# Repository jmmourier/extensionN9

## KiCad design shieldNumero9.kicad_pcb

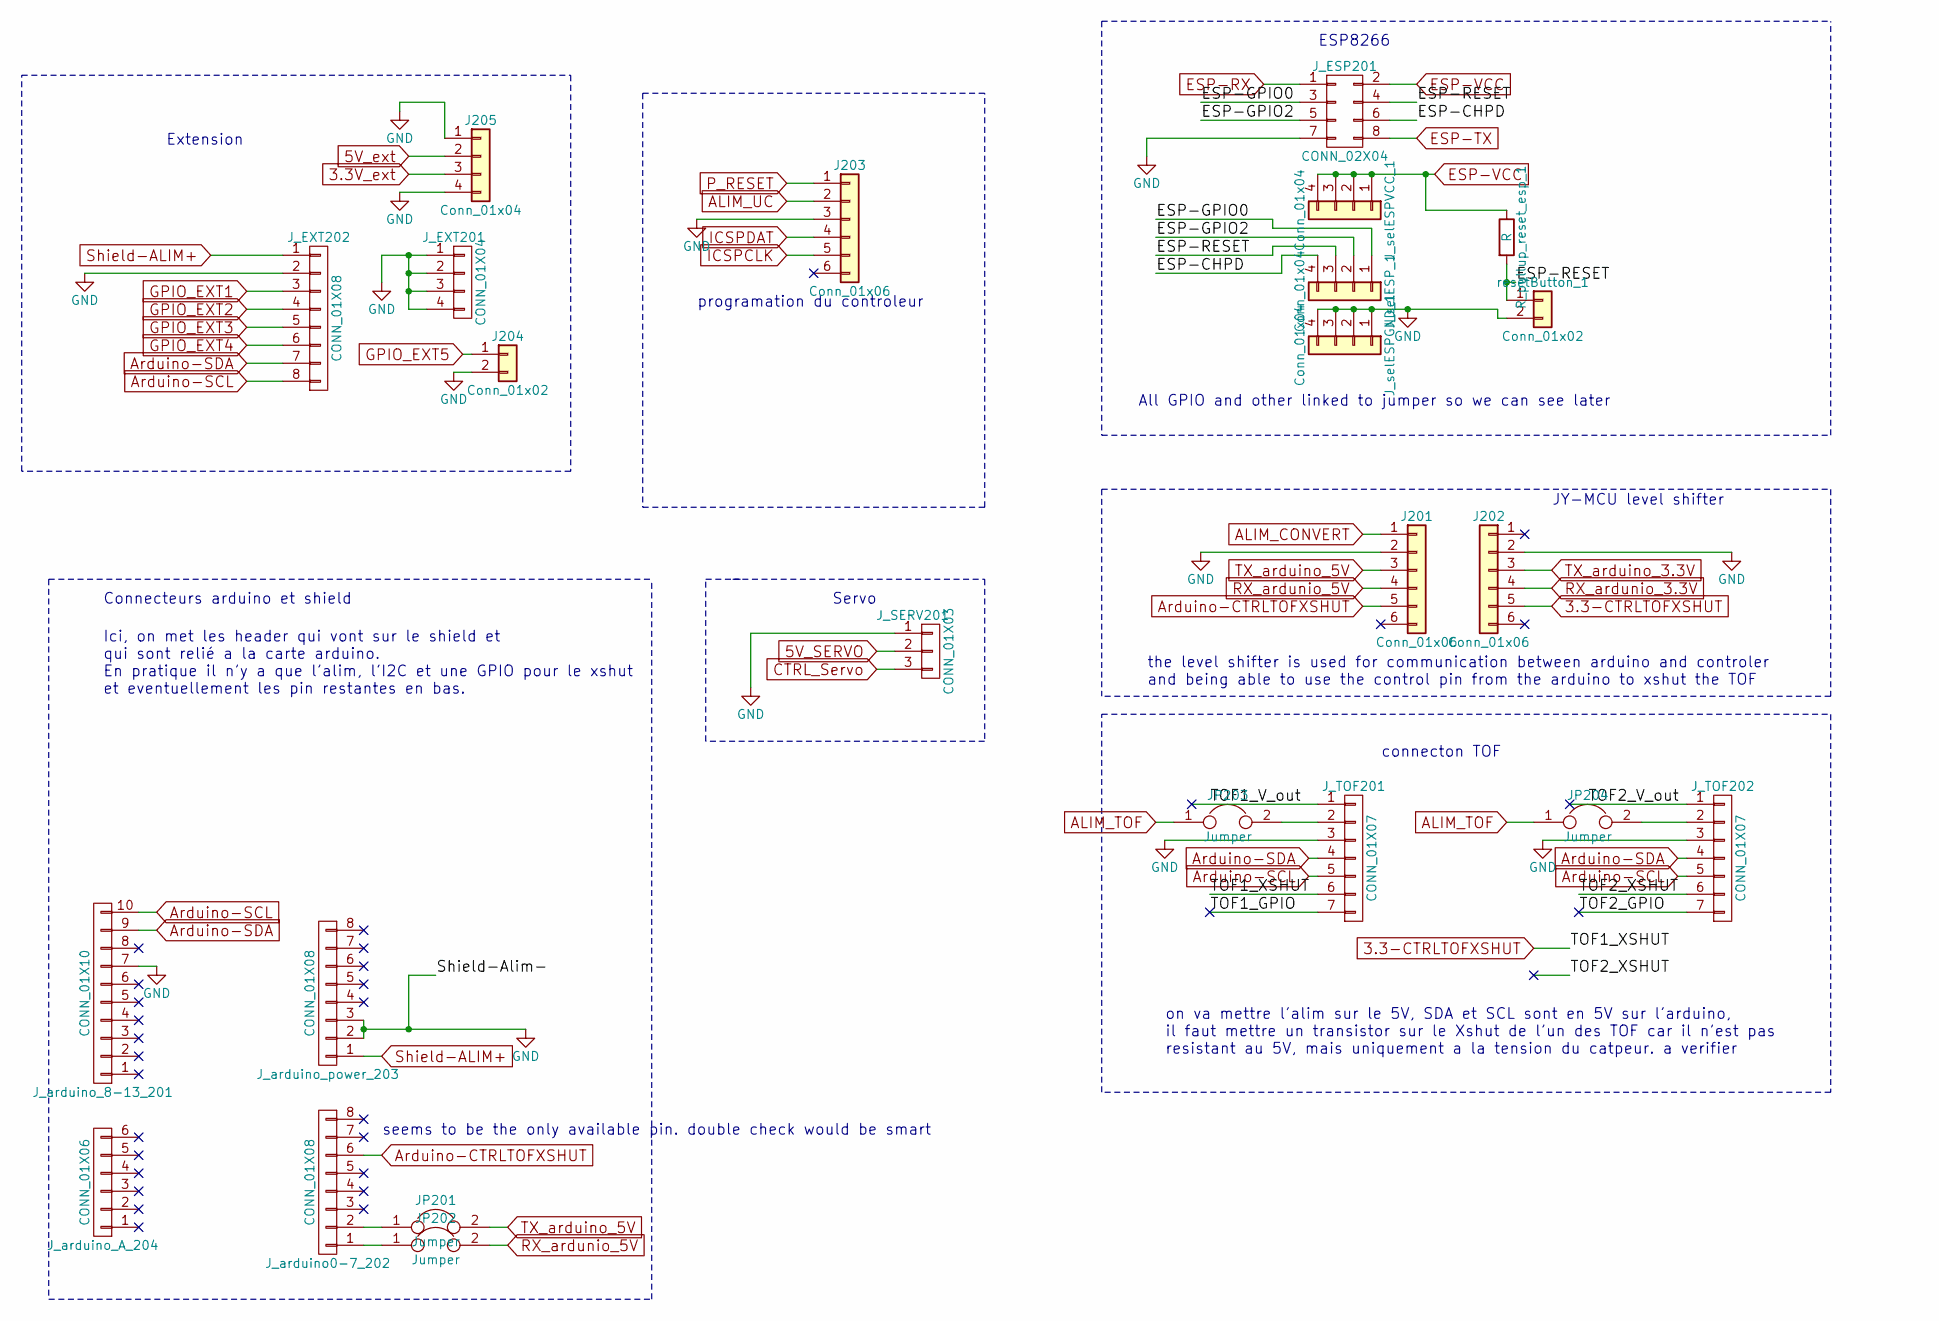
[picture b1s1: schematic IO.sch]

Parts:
J201, J202: Conn_01x06; Socket_Strip_Straight_1x06_Pitch2.54mm
J203: Conn_01x06; Pin_Header_Straight_1x06_Pitch2.54mm
J204: Conn_01x02; Pin_Header_Straight_1x02_Pitch2.54mm
J205: Conn_01x04; Socket_Strip_Straight_1x04_Pitch2.54mm
JP201, JP202, JP203, JP204: Jumper; Pin_Header_Straight_2x01_Pitch2.54mm
J_ESP201: CONN_02X04; Socket_Strip_Straight_2x04_Pitch2.54mm
J_EXT201: CONN_01X04; Socket_Strip_Straight_1x04_Pitch2.54mm
J_EXT202: CONN_01X08; Socket_Strip_Straight_1x08_Pitch2.54mm
J_SERV201: CONN_01X03; Socket_Strip_Straight_1x03_Pitch2.54mm
J_TOF201, J_TOF202: CONN_01X07; Socket_Strip_Straight_1x07_Pitch2.54mm
J_arduino0-7_202: CONN_01X08; Socket_Strip_Straight_1x08_Pitch2.54mm
J_arduino_8-13_201: CONN_01X10; Socket_Strip_Straight_1x10_Pitch2.54mm
J_arduino_A_204: CONN_01X06; Socket_Strip_Straight_1x06_Pitch2.54mm
J_arduino_power_203: CONN_01X08; Socket_Strip_Straight_1x08_Pitch2.54mm
J_selESPGND_1: Conn_01x04; Socket_Strip_Straight_1x04_Pitch2.54mm
J_selESPVCC_1: Conn_01x04; Socket_Strip_Straight_1x04_Pitch2.54mm
J_selESP_1: Conn_01x04; Socket_Strip_Straight_1x04_Pitch2.54mm
R_pullup_reset_esp_1: R; R_Axial_DIN0207_L6.3mm_D2.5mm_P7.62mm_Horizontal
resetButton_1: Conn_01x02; Pin_Header_Angled_1x02_Pitch2.54mm

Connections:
3.3-CTRLTOFXSHUT: J202.5, J_TOF201.6
/IO shield/ESP-CHPD: J_ESP201.6, J_selESP_1.4
/IO shield/ESP-GPIO0: J_ESP201.3, J_selESP_1.1
/IO shield/ESP-GPIO2: J_ESP201.5, J_selESP_1.2
/IO shield/ESP-RESET: J_ESP201.4, J_selESP_1.3, R_pullup_reset_esp_1.2, resetButton_1.1
/IO shield/TOF1_GPIO: J_TOF201.7
/IO shield/TOF1_V_out: J_TOF201.1
/IO shield/TOF2_GPIO: J_TOF202.7
/IO shield/TOF2_V_out: J_TOF202.1
/IO shield/TOF2_XSHUT: J_TOF202.6
Arduino-CTRLTOFXSHUT: J201.5, J_arduino0-7_202.6
Arduino-SCL: J_EXT202.8, J_TOF201.5, J_TOF202.5, J_arduino_8-13_201.10
Arduino-SDA: J_EXT202.7, J_TOF201.4, J_TOF202.4, J_arduino_8-13_201.9
CTRL_Servo: J_SERV201.3; also elsewhere on the board
ESP-RX: J_ESP201.1; also elsewhere on the board
ESP-TX: J_ESP201.8; also elsewhere on the board
GND: J201.2, J202.2, J203.3, J204.2, J205.1, J205.4, J_ESP201.7, J_EXT201.1, J_EXT201.2, J_EXT201.3, J_EXT201.4, J_EXT202.2, J_SERV201.1, J_TOF201.3, J_TOF202.3, J_arduino_8-13_201.7, J_arduino_power_203.2, J_arduino_power_203.3, J_selESPGND_1.1, J_selESPGND_1.2, J_selESPGND_1.3, J_selESPGND_1.4, resetButton_1.2; also elsewhere on the board
GPIO_EXT1: J_EXT202.3; also elsewhere on the board
GPIO_EXT2: J_EXT202.4; also elsewhere on the board
GPIO_EXT3: J_EXT202.5; also elsewhere on the board
GPIO_EXT4: J_EXT202.6; also elsewhere on the board
GPIO_EXT5: J204.1; also elsewhere on the board
ICSPCLK: J203.5; also elsewhere on the board
ICSPDAT: J203.4; also elsewhere on the board
unnamed: JP201.1, J_arduino0-7_202.2
unnamed: JP202.1, J_arduino0-7_202.1
unnamed: JP203.2, J_TOF201.2
unnamed: JP204.2, J_TOF202.2
P_RESET: J203.1; also elsewhere on the board
RX_ardunio_3.3V: J202.4; also elsewhere on the board
RX_ardunio_5V: J201.4, JP202.2
Shield-ALIM+: J_EXT202.1, J_arduino_power_203.1; also elsewhere on the board
TX_arduino_3.3V: J202.3; also elsewhere on the board
TX_arduino_5V: J201.3, JP201.2

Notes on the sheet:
Servo
Connecteurs arduino et shield
Ici, on met les header qui vont sur le shield et qui sont relié a la carte arduino. En pratique il n'y a que l'alim, l'I2C et une GPIO pour le xshut et eventuellement les pin restantes en bas.
Extension
connecton TOF
ESP8266
on va mettre l'alim sur le 5V, SDA et SCL sont en 5V sur l'arduino, il faut mettre un transistor sur le Xshut de l'un des TOF car il n'est pas resistant au 5V, mais uniquement a la tension du catpeur. a verifier
programation du controleur
JY-MCU level shifter
the level shifter is used for communication between arduino and controler and being able to use the control pin from the arduino to xshut the TOF
All GPIO and other linked to jumper so we can see later
seems to be the only available pin. double check would be smart

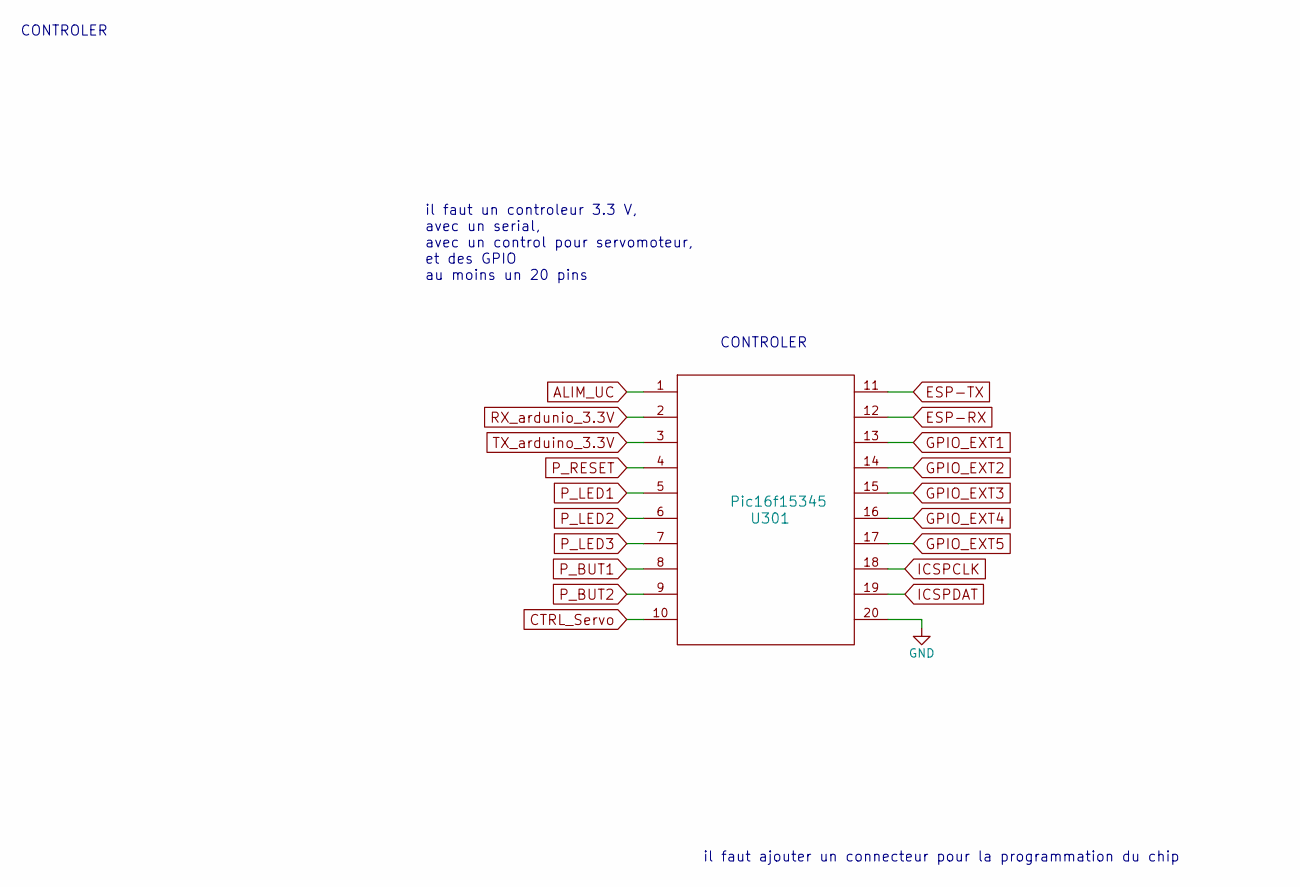
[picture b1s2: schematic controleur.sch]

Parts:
U301: Pic16f15345; DIP-20_W7.62mm_LongPads

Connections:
CTRL_Servo: U301.10; also elsewhere on the board
ESP-RX: U301.12; also elsewhere on the board
ESP-TX: U301.11; also elsewhere on the board
GND: U301.20; also elsewhere on the board
GPIO_EXT1: U301.13; also elsewhere on the board
GPIO_EXT2: U301.14; also elsewhere on the board
GPIO_EXT3: U301.15; also elsewhere on the board
GPIO_EXT4: U301.16; also elsewhere on the board
GPIO_EXT5: U301.17; also elsewhere on the board
ICSPCLK: U301.18; also elsewhere on the board
ICSPDAT: U301.19; also elsewhere on the board
P_BUT1: U301.8; also elsewhere on the board
P_BUT2: U301.9; also elsewhere on the board
P_LED1: U301.5; also elsewhere on the board
P_LED2: U301.6; also elsewhere on the board
P_LED3: U301.7; also elsewhere on the board
P_RESET: U301.4; also elsewhere on the board
RX_ardunio_3.3V: U301.2; also elsewhere on the board
TX_arduino_3.3V: U301.3; also elsewhere on the board

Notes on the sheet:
CONTROLER
il faut un controleur 3.3 V, avec un serial, avec un control pour servomoteur, et des GPIO au moins un 20 pins
il faut ajouter un connecteur pour la programmation du chip

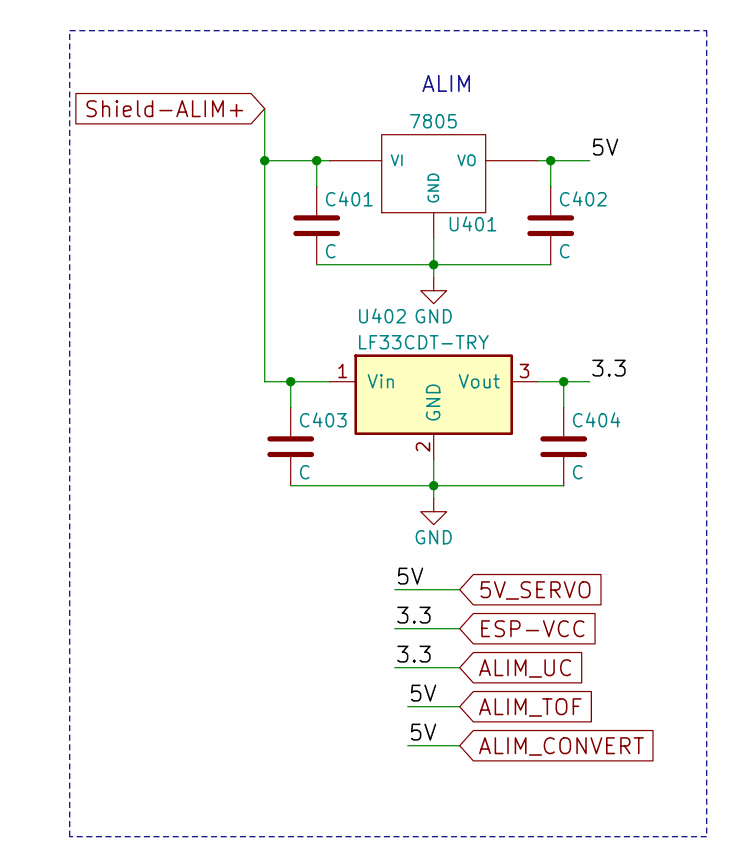
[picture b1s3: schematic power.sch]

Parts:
C401, C402, C403, C404: C
U401: 7805; TO-220
U402: LF33CDT-TRY; TO-220

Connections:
GND: C401.2, C402.2, C403.2, C404.2, U401.2 (GND), U402.2 (GND); also elsewhere on the board
Shield-ALIM+: C401.1, C403.1, U401.1 (VI), U402.1 (Vin); also elsewhere on the board

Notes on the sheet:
ALIM

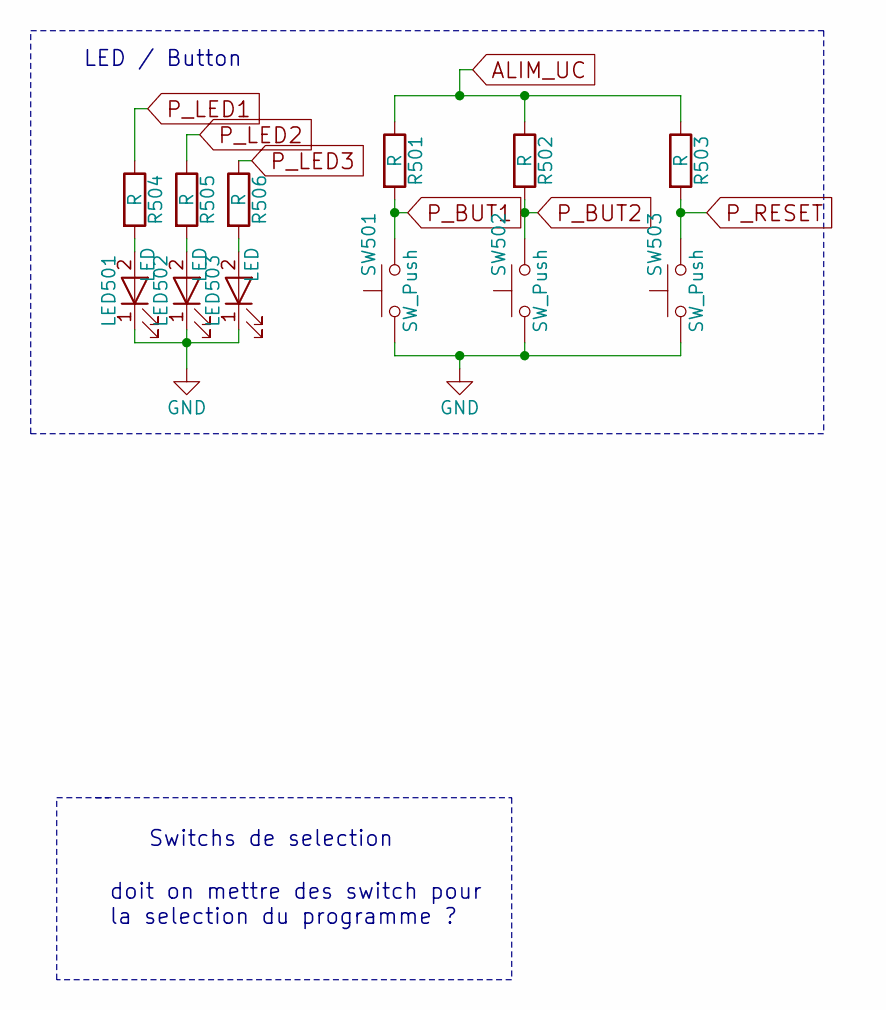
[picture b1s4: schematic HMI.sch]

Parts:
LED501, LED502, LED503: LED; LED_D5.0mm
R501, R502, R503, R504, R505, R506: R; R_Axial_DIN0207_L6.3mm_D2.5mm_P7.62mm_Horizontal
SW501, SW502, SW503: SW_Push; SW_PUSH_6mm

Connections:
GND: LED501.1 (K), LED502.1 (K), LED503.1 (K), SW501.1, SW502.1, SW503.1; also elsewhere on the board
unnamed: LED501.2 (A), R504.2
unnamed: LED502.2 (A), R505.2
unnamed: LED503.2 (A), R506.2
P_BUT1: R501.2, SW501.2; also elsewhere on the board
P_BUT2: R502.2, SW502.2; also elsewhere on the board
P_LED1: R504.1; also elsewhere on the board
P_LED2: R505.1; also elsewhere on the board
P_LED3: R506.1; also elsewhere on the board
P_RESET: R503.2, SW503.2; also elsewhere on the board

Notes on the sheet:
Switchs de selection
LED / Button
doit on mettre des switch pour la selection du programme ?

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
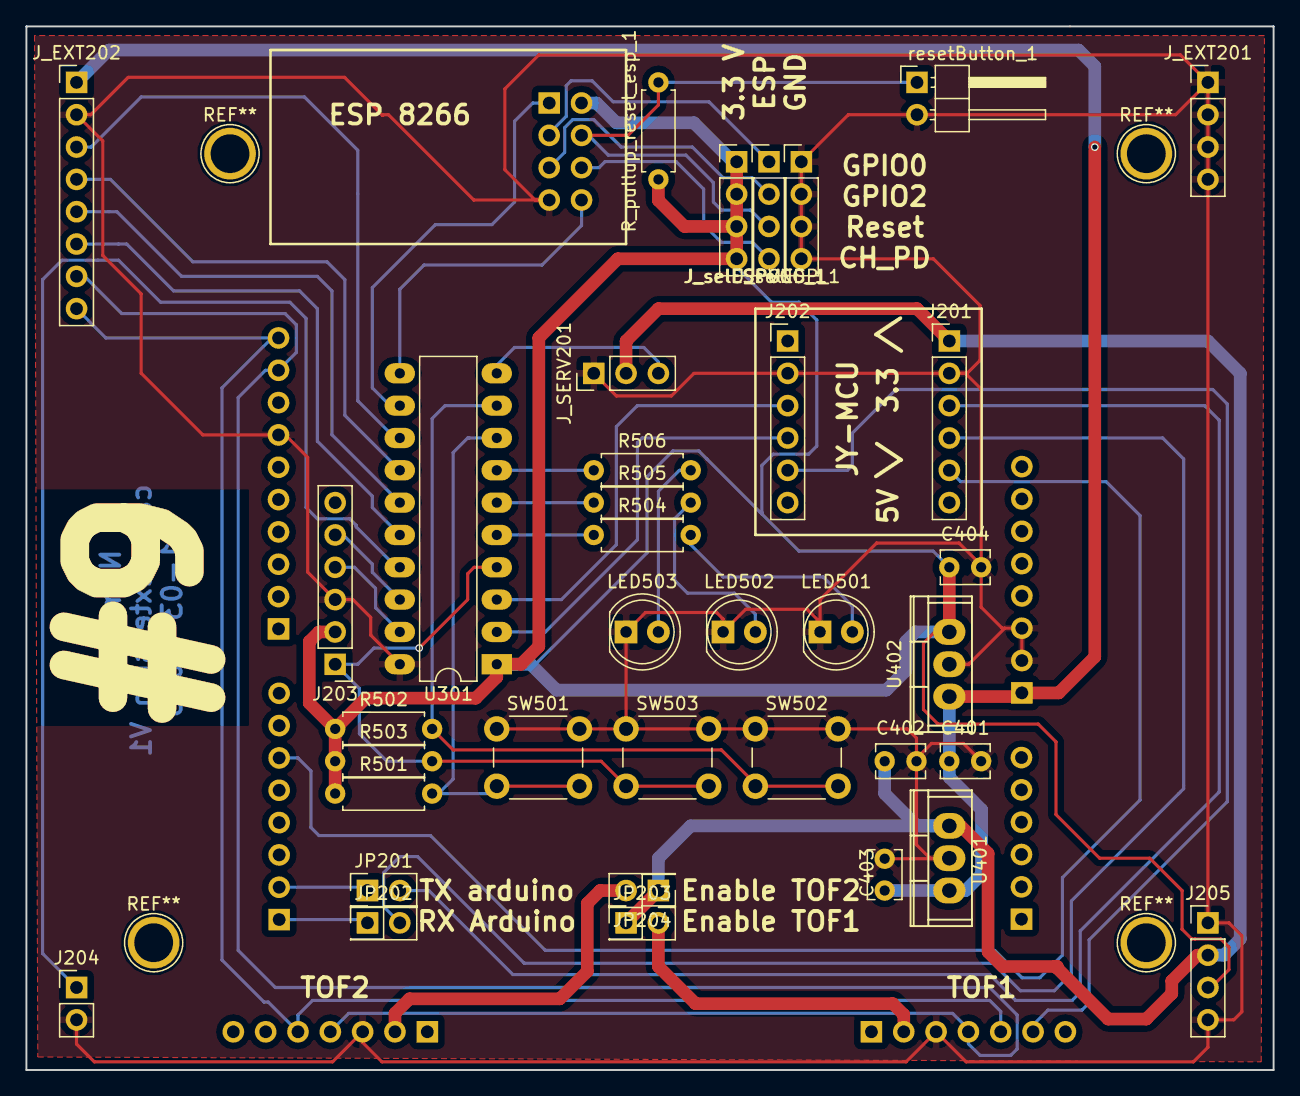
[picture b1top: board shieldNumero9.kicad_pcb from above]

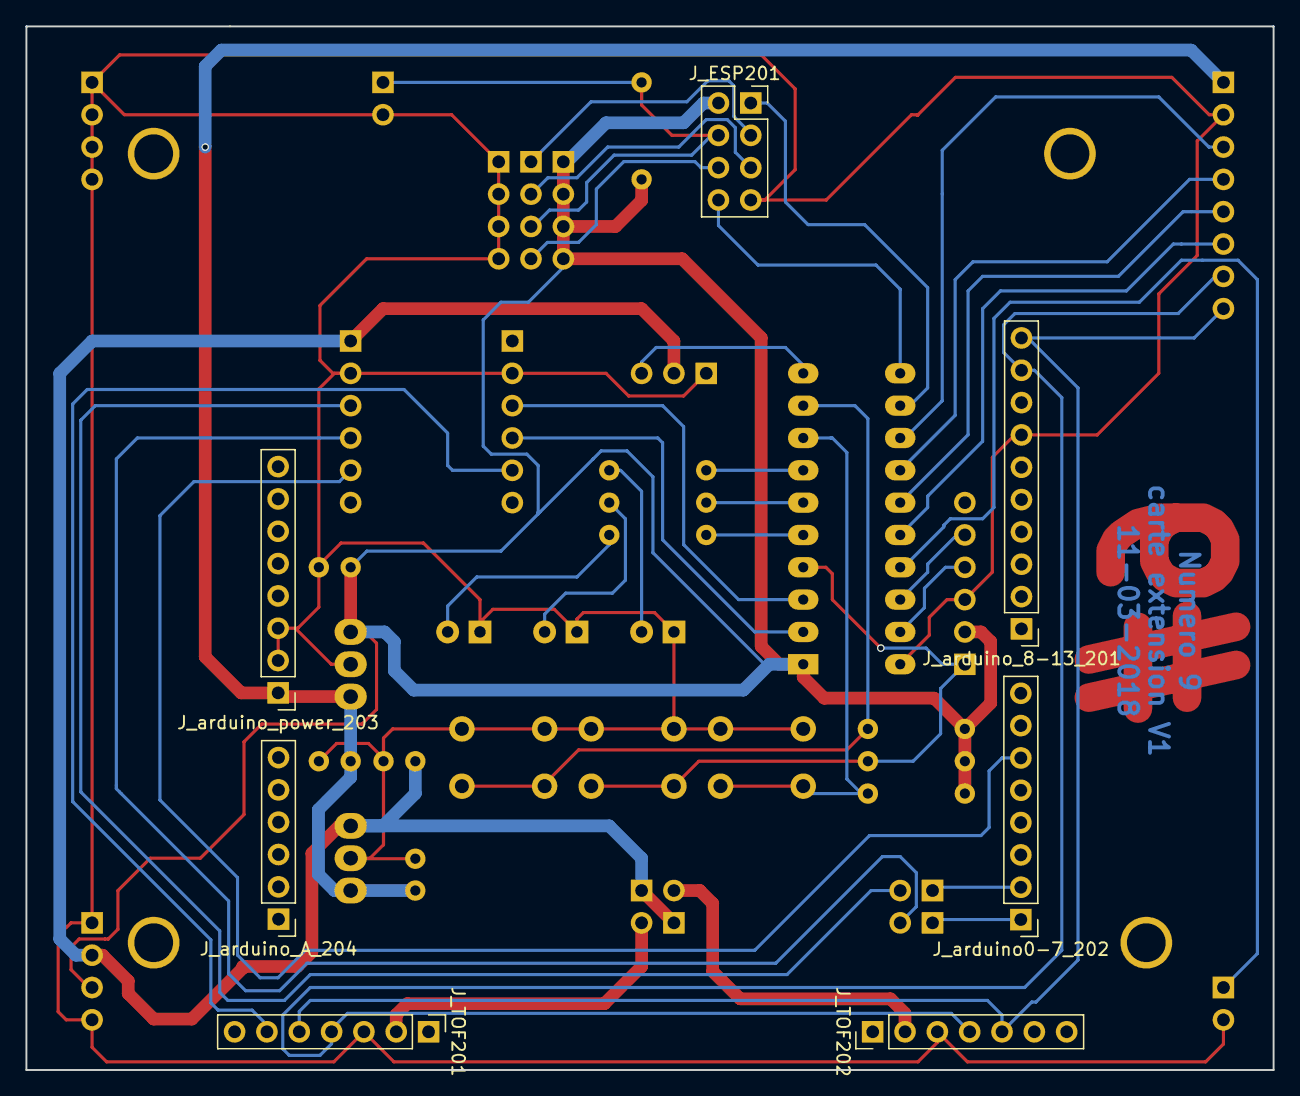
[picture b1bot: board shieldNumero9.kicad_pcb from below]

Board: 2 copper layers, 98.0 x 82.0 mm, 43 parts (7 on the bottom side), 39 nets.

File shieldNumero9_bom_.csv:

Component,Description,Part,References,Value,Footprint,Quantity Per PCB,Datasheet
1,Unpolarized capacitor,C,C401 C402 C403 C404,C,,4,
2,,CONN_01X03,J_SERV201,CONN_01X03,Socket_Strip_Straight_1x03_Pitch2.54mm,1,
3,,CONN_01X04,J_EXT201,CONN_01X04,Socket_Strip_Straight_1x04_Pitch2.54mm,1,
4,,CONN_01X06,J_arduino_A_204,CONN_01X06,Socket_Strip_Straight_1x06_Pitch2.54mm,1,
5,,CONN_01X07,J_TOF201 J_TOF202,CONN_01X07,Socket_Strip_Straight_1x07_Pitch2.54mm,2,
6,,CONN_01X08,J_EXT202 J_arduino_power_203,CONN_01X08,Socket_Strip_Straight_1x08_Pitch2.54mm,2,
7,,CONN_01X08,J_arduino0-7_202,CONN_01X08,Pin_Header_Straight_1x08_Pitch2.54mm,1,
8,,CONN_01X10,J_arduino_8-13_201,CONN_01X10,Socket_Strip_Straight_1x10_Pitch2.54mm,1,
9,,CONN_02X04,J_ESP201,CONN_02X04,Socket_Strip_Straight_2x04_Pitch2.54mm,1,
10,"Generic connector, single row, 01x04",Conn_01x04,J_selESPGND_1 J_selESPVCC_1 J_selESP_1,Conn_01x04,Socket_Strip_Straight_1x04_Pitch2.54mm,3,
11,LED generic,LED,LED501 LED502 LED503,LED,,3,
12,Resistor,R,R501 R502 R503 R504 R505 R506 R_pullup_reset_esp_1,R,,7,
13,"Push button switch, generic, two pins",SW_Push,SW501 SW502 SW503,SW_Push,,3,
14,,7805,U401,7805,TO-220,1,
15,,LF33CDT-TRY,U402,LF33CDT-TRY,TO-220,1,
16,"Generic connector, single row, 01x02",Conn_01x02,resetButton_1,Conn_01x02,,1,





Component Groups:,16
Component Count:,33
Fitted Components:,33
Number of PCBs:,1
Total components:,33
Schematic Version:,
Schematic Date:,
BoM Date:,25/02/2018 19:16:37
Schematic Source:,D:/PROJETS/numero9/carteExtension/shieldNumero9.sch
KiCad Version:,Eeschema 4.0.7

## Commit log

2018-02-28 initial commit, bases of the board
2018-03-04 finish schematics. add componants, find right chip, firest verification OK, ready for routing
2018-03-10 placement componants seems OK
2018-03-10 finish routing, need to double check
2018-03-13 add file for fab
2018-03-27 add latest version, board v1 has been released
